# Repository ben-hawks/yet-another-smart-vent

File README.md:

# Yet Another Smart Vent

This project contains most everything needed to 3D print, assemble, and flash an ESPHome/MQTT Smart Vent.

[Here is a short video demonstration on YouTube.](https://youtu.be/ANneINQjgso) 
(Consider subscribing for future updates)

## Getting Started
1. Electronics:
    - [Components List](/docs/ELECTRONIC_COMPONENTS.md)
    - [Assembly Instructions](/docs/ELECTRONICS_ASSEMBLY.md)
2. 3D Printing:
    - [Printing Advice](/docs/VENT_PRINTING.md)
    - [STLs](https://www.printables.com/social/337332-tonyb/collections/241144?o=download_count):
        - [2x6 Vent](https://www.printables.com/model/347800-yet-another-smart-vent-2x6)
        - [2x10 Vent](https://www.printables.com/model/259777-yet-another-smart-vent-2x10)
        - [2x12 Vent](https://www.printables.com/model/260300-yet-another-smart-vent-2x12)
        - [3x10 Vent](https://www.printables.com/model/262311-yet-another-smart-vent-3x10)
        - [4x10 Vent](https://www.printables.com/model/259241-yet-another-smart-vent-4x10)
        - [4x12 Vent](https://www.printables.com/model/259924-yet-another-smart-vent-4x12)
        - [4x14 Vent](https://www.printables.com/model/334635-yet-another-smart-vent-4x14)
        - [6x8   Vent](https://www.printables.com/model/264778-yet-another-smart-vent-6x8)
        - [6x10 Vent](https://www.printables.com/model/259323-yet-another-smart-vent-6x10)
        - [6x12 Vent](https://www.printables.com/model/259622-yet-another-smart-vent-6x12)
        - [ESP D1 Mini Shield Solder Spacer](https://www.printables.com/model/259295-esp-d1-mini-shield-solder-spacer)
    - [Assembly Instructions](/docs/VENT_ASSEMBLY.md)
3. [Compile and Upload Instructions](/docs/COMPILE_AND_UPLOAD.md)
4. [Setup and Testing](/docs/SETUP_AND_TESTING.md)
6. [Implementation Options](/docs/IMPLEMENTATION_OPTIONS.md)

## Battery + Thread variant (work in progress)
A battery-powered 2x12 variant using a Seeed XIAO ESP32-C6 on Thread, with a
power-gated servo and an original parametric OpenSCAD model built around M3
heat-set inserts. See [docs/BATTERY_THREAD.md](/docs/BATTERY_THREAD.md).
A matching Thread rewrite of Delta Tango (supply/return temperature + a vent
safety blueprint) lives in [delta-tango/](/delta-tango/README.md).

A 6" round **ceiling** vent with louvers and a battery pod beside it:
[docs/ROUND_CEILING_VENT.md](/docs/ROUND_CEILING_VENT.md).

## Important Recommendations
- It is recommended that you pair this vent with a system that can [measure and monitor Delta T](https://www.youtube.com/watch?v=_pD-rRCNv8k) (the difference in HVAC return air temperature and supply air temperature). Check out the [Delta Tango](https://github.com/BrobstonCreations/delta-tango) project.
- It is recommended to install a [Static Pressure Regulating Damper](https://www.zonefirst.com/product/sprddd/), which goes between the return air plenum and the supply air plenum. This damper acts as a bypass and will open or close relative to the backpressure change created by opening and closing vents. This will relieve the majority of the back pressure that is created by closing vents and will help to ensure the longevity of the blower.

## Future Features
- Create 8x14 variation.
- Fix a small bug where ESPHome's Servo Position does not match up with the Servo's Potentiometer's position after physically moving the vent's louvers.
- Investigate power saving options for battery pack use.
- Add functionality to open vent if the central vent control system goes offline.
- Experiment with 12x12 vent.

## Philosophy
- Local Control
- External Integration
- Easy of Use
- Community Feedback
- Community Contributions
- Agile, Lean, and Extreme Programming Practices
- Mostly Decentralized Manufacturing

## Pull Requests
Pull Requests are always welcome. I would recommend starting with an [issue](https://github.com/TonyBrobston/yet-another-smart-vent/issues), so that we can discuss viability and implementation.

## Issues
Feel free to open an [issue](https://github.com/TonyBrobston/yet-another-smart-vent/issues) and I will respond as I have time. The hope is to create a system that gives consumers what they want, your feedback is important. 

## Build
If you want to build this manually using docker, run this the command from within this git repo cloned to your machine: 
```
docker run -v .:/config esphome/esphome compile yet-another-smart-vent-dfrobot-dms-mg90-a.yaml
```
After this command runs, `firmware.bin` will be created at this path from the current directory: `.esphome/build/yet-another-smart-vent/.pioenvs/yet-another-smart-vent/firmware.bin`.

## Support
If you like the work I do and want to give back, consider [buying me a coffee ☕](https://www.buymeacoffee.com/brocreates) or making a donation via [PayPal](https://www.paypal.com/donate/?hosted_button_id=BXK8JW6A2FZLE) or [Stripe](https://buy.stripe.com/7sI7t03JC9GUf4c6oo).

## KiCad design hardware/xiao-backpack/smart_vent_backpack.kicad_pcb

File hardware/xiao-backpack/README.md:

# Smart Vent XIAO backpack (KiCad)

A 48 × 19 mm two-layer board that holds all of the vent's auxiliary
circuitry. The XIAO ESP32-C6 plugs onto it with its two 1×7 headers.

**Status: v0.2, routed and checked, not yet built.** It was autorouted with
Freerouting from `fab/smart_vent_backpack.dsn`; the result is in
`fab/smart_vent_backpack.ses`. After importing:
- every net is connected (0 unconnected pads)
- KiCad DRC reports 0 violations (KiCad 7 here, and KiCad 10 on a second
  machine), against fab rules of 0.3 mm to the edge, 0.15 mm clearance and
  0.13 mm minimum track
- the PCB's netlist matches the schematic's
- an independent review with KiCad 10 found no blockers (see
  [Design review notes](#design-review-notes-v02))

Power nets (VBAT_RAW, VBAT, GND, VSW, SW, V5) are 0.6 mm, narrowing to
0.45 mm only for a few millimetres at pads. Ground is poured on both
layers. Order with [`fab/gerbers.zip`](fab/gerbers.zip) (2 layers, 1.6 mm,
1 oz, any colour; JLCPCB's standard tier is enough).

## Circuit

| Block | Parts | Notes |
|---|---|---|
| Battery in | J1 (JST-PH 2 mm), Q1 AO3401A, TP1/TP2 | Q1 blocks a cell fitted backwards and conducts both ways otherwise. TP1/TP2 are wire pads. Run short wires through the window to the XIAO's BAT+/BAT− pads, which charge the cell over USB-C |
| Servo power switch | U1 TPS22917 load switch, C1, C2 (1 nF, CT to VIN: about 1.6 ms soft start), R1 (keeps it off) | Cuts the cell off completely between moves (nanoamp leakage). Its ON pin is XIAO **D3** |
| 5 V boost | U2 MT3608, L1 10 µH, D1 SS34, C3–C5 22 µF, R2/R3 | Vout = 0.6 V × (1 + 51k/6.8k) = 5.1 V (both JLCPCB basic parts). Only powered while U1 is on |
| Servo | J2: GND, +5V, SIG, FB | SIG from **D2** through R8 (330 Ω). FB through a 10k/20k divider (R6/R7, C7 filter) to **D1**: 5.1 V → 3.4 V. Feetech's sheet shows the FT90M-FB's feedback reaching **4.45 V**, so it must be divided |
| Battery sense | R4/R5 1M/1M, C6 | To **D0**. Draws about 2 µA |
| Limit switch | J3 | Fed from **D3** through R9 (1 kΩ), returns to **D4** with R10 (100 kΩ) pull-down. Only live while the servo is powered |

These pins match `common/smart-vent-thread-battery-base.yaml`, so the
firmware needs no changes.

## Building it

- All passives are 0805 (1206 for the 22 µF capacitors) with hand-solder
  pads. Both ICs are SOT-23-6. Parts list: [`fab/bom.csv`](fab/bom.csv).
- **Inductor:** any shielded 10 µH in 6 × 6 mm with a saturation current of
  2.5 A or more. A stalled servo pulls about 1.3 A from the cell through the
  boost converter.
- **Battery connector polarity:** JST-PH leads aren't standardized. Pin 1
  (square pad) is **+**. Check your cell's leads before plugging in.
- Mount the XIAO on the **top** with standard headers. Only the 0805 parts
  sit underneath it. Solder the battery wires to the XIAO's BAT pads before
  stacking the boards.

## JLCPCB assembly (PCBA)

Upload these three to JLCPCB with **PCB Assembly** turned on (top side, Economic):

| File | What |
|---|---|
| [`fab/gerbers.zip`](fab/gerbers.zip) | Board |
| [`fab/jlcpcb/bom_jlcpcb.csv`](fab/jlcpcb/bom_jlcpcb.csv) | Comment, Designator, Footprint, LCSC Part # |
| [`fab/jlcpcb/cpl_jlcpcb.csv`](fab/jlcpcb/cpl_jlcpcb.csv) | Designator, Mid X, Mid Y, Layer, Rotation |

- **What JLCPCB places:** all 22 SMD parts. 14 BOM lines are JLCPCB
  **Basic** parts. 3 are **Extended**, which carries a feeder fee per order:
  TPS22917DBVR (C2681320), MT3608 (C84817) and SRN6045TA-100M (C2046332).
  Part numbers and stock were checked against JLCPCB's parts library on
  2026-11-01.
- **Left for you:** the through-hole parts (J1 JST-PH C131337, J2, J3, the
  XIAO socket headers and the TP1/TP2 wire pads) aren't in the files. Solder
  them yourself, or add them to the order if you want JLCPCB's through-hole
  service.
- **Rotations:** the CPL applies JLCPCB's usual +180° for SOT-23 parts. In
  JLCPCB's placement preview, **check that pin 1 of U1 and U2 and the
  cathode band of D1 sit on the marked pads** before confirming. Rotate any
  part that's off there; the files don't need regenerating.

## Design review notes (v0.2)

- **C2 now goes from CT to VIN and is fitted** (TI SLVSDW8B, Table 6-1).
  v0.1 wired it to GND and left it off. With CT open the switch rises in
  about 65 µs, which charges C3–C5 through L1 and D1 at roughly 2 A, close
  to the TPS22917's 2.5 A pulse rating. With 1 nF it rises in about 1.6 ms
  and the inrush is about 0.15 A.
- **Q1 (AO3401A) is new:** drain to the cell, source to the board, gate to
  GND. A reversed cell leaves it off. Don't plug in USB while a cell is
  reversed: the XIAO's charger would turn Q1 on.
- The servo header's pin labels (G, 5V, S, FB) are on the **back**
  silkscreen; Q1 and C2 took their place on the front.
- **Independent KiCad 10 review (2026-11-13):** pinouts of U1, U2, Q1 and
  D1, the XIAO pin map, all three dividers and the five LCSC numbers for
  the active parts and inductor were re-checked against datasheets and
  distributor listings; no errors. KiCad's ERC flags U1's QOD pin tied to
  VOUT and an analyzer flags U2's EN tied to IN; both are the
  manufacturers' documented connections. Its three layout points were
  checked here: one 0.125 mm neck on LIMIT is now 0.13 mm (JLCPCB's
  standard minimum is 0.127 mm); the "0.1 mm from the edge" on J2/J3 is
  their courtyard, and the nearest pad copper to any edge is 0.68 mm; the
  0.45 mm necks on the battery nets total under 8 mm.
- The router is now given a 0.35 mm keep-out around the battery window and
  along the board edges, so it can't hug them (it did in v0.1).
- **Checked against datasheets:** the TPS22917 and MT3608 pinouts, the
  MT3608 FB voltage (0.6 V), EN tied to the input (allowed), and the input
  range (2–24 V). GPIO0/1 are ADC1 channels 0/1. None of the pins used
  (GPIO0, 1, 2, 21, 22) is a strapping pin; those are GPIO4, 5, 8, 9 and 15.
- **Fit in the vent tower:** solder the XIAO **directly** onto its male
  headers (no female sockets), and use **right-angle** headers for J2/J3.
  The pads are the same, and this keeps the stack inside the 17 mm between
  the cell holder and the partition (1 mm and 0.9 mm clearance). Trim the
  through-hole leads on the back to about 2 mm.
- **Battery wire window:** its position comes from Seeed's description
  ("near D5 / D8"). If the BAT pads end up off the window, route the two
  wires around the board edge to TP1/TP2.

## Hand soldering

Everything is hand-solderable with a fine-tip iron, flux and tweezers:
- 0805 and 1206 parts on KiCad's hand-solder pads.
- Both ICs are SOT-23-6 (0.95 mm pitch) on the hand-solder variant.
- The inductor's terminals are mostly under its body, so its pads extend
  0.8 mm past the Bourns land pattern for the iron. Tin one pad, place the
  part, then heat the extended pad until solder wicks under.
- No vias sit in pads, and ground pads use thermal spokes, so they heat up
  normally.

Suggested order:
1. The low parts under the XIAO (R1, R4–R10, C6, C7). They're unreachable
   once the XIAO is fitted.
2. Q1, U1, U2, C1–C5, R2, R3, D1, then L1.
3. Before fitting the XIAO, check that 5 V comes up: connect the cell and
   pull D3 (SRV_EN) high through about 1 kΩ. J2 pin 2 should read about
   5.1 V, and about 0 V again once D3 is released.
4. J1, J2 and J3 (right-angle), then the XIAO, soldered directly on its
   male headers. Solder the battery wires to
   the XIAO's BAT pads, pass them through the window, and solder them to
   TP1 (+) and TP2 (−).

## Routing

`generate.py` builds everything from one parts table: the schematic (net
labels on every pin), the placed PCB, net classes (0.6 mm for power nets),
ground pours, Gerbers, the parts list, and the checks (schematic vs PCB
nets, DRC).

```bash
/usr/bin/python3 generate.py                              # place, write fab/smart_vent_backpack.dsn
# route fab/smart_vent_backpack.dsn with Freerouting (or similar) -> .ses
/usr/bin/python3 generate.py --ses fab/smart_vent_backpack.ses   # import routes, pour, DRC, Gerbers
# GND tracks that hug the battery window are dropped on import (the pours carry GND)
```

The router's output can also be imported straight into KiCad (**File →
Import → Specctra Session**) on the generated `.kicad_pcb`.

Requires KiCad 7 or 8. On KiCad 10 the script stops: the Bourns inductor
footprint it adapts has changed and the `Q_PMOS_GSD` symbol was renamed.
The generated project files open fine in KiCad 10. Set `KICAD7_FOOTPRINT_DIR` if KiCad's global
libraries aren't configured.

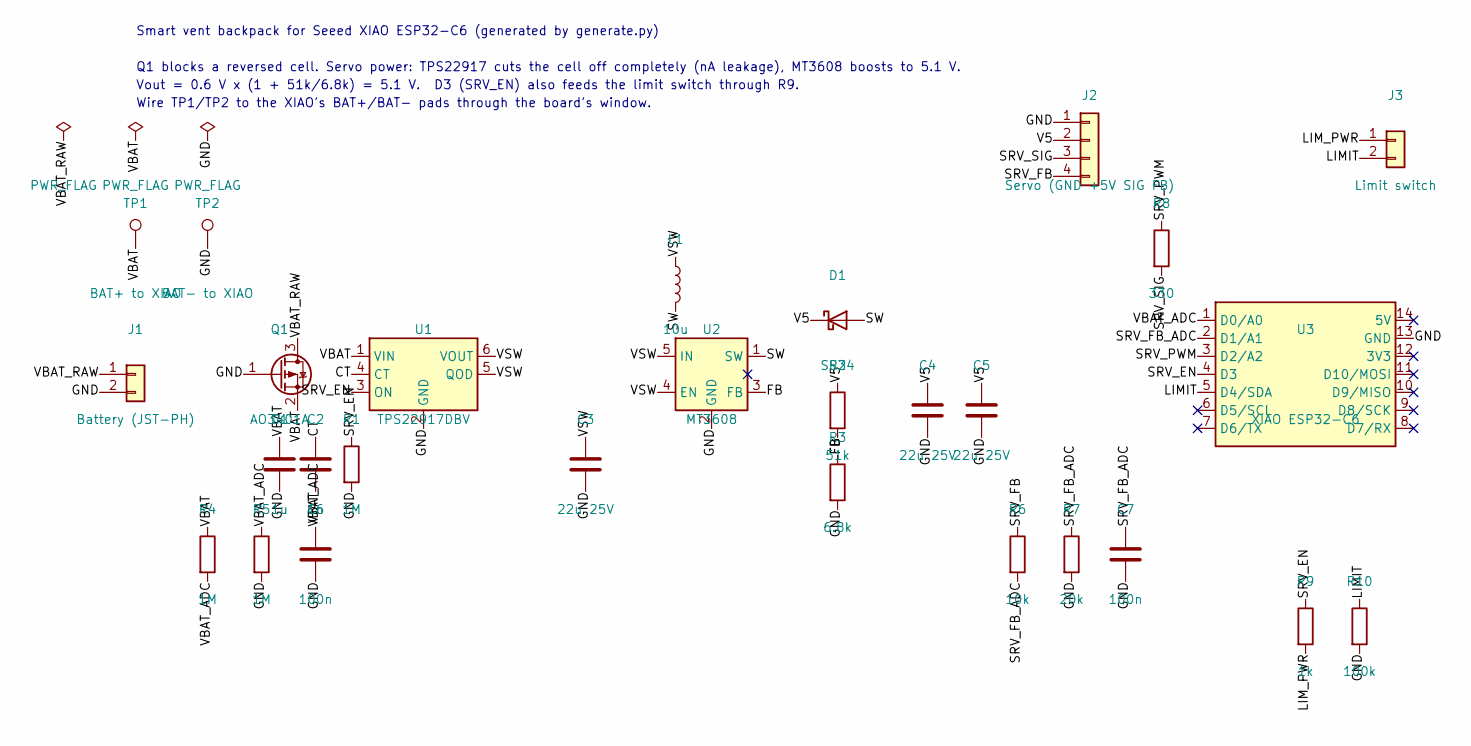
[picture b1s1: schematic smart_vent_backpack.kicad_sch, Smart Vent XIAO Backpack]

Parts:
C1: 1u; C_0805_2012Metric_Pad1.18x1.45mm_HandSolder
C2: 1n; C_0805_2012Metric_Pad1.18x1.45mm_HandSolder
C3, C4, C5: 22u 25V; C_1206_3216Metric_Pad1.33x1.80mm_HandSolder
C6, C7: 100n; C_0805_2012Metric_Pad1.18x1.45mm_HandSolder
D1: SS34; D_SMA_Handsoldering
J1: Battery (JST-PH); JST_PH_B2B-PH-K_1x02_P2.00mm_Vertical
J2: Servo (GND +5V SIG FB); PinHeader_1x04_P2.54mm_Vertical
J3: Limit switch; PinHeader_1x02_P2.54mm_Vertical
L1: 10u; L_Bourns_SRN6045TA_HandSolder
Q1: AO3401A; SOT-23
R1, R4, R5: 1M; R_0805_2012Metric_Pad1.20x1.40mm_HandSolder
R2: 51k; R_0805_2012Metric_Pad1.20x1.40mm_HandSolder
R3: 6.8k; R_0805_2012Metric_Pad1.20x1.40mm_HandSolder
R6: 10k; R_0805_2012Metric_Pad1.20x1.40mm_HandSolder
R7: 20k; R_0805_2012Metric_Pad1.20x1.40mm_HandSolder
R8: 330; R_0805_2012Metric_Pad1.20x1.40mm_HandSolder
R9: 1k; R_0805_2012Metric_Pad1.20x1.40mm_HandSolder
R10: 100k; R_0805_2012Metric_Pad1.20x1.40mm_HandSolder
TP1: BAT+ to XIAO; TestPoint_THTPad_1.5x1.5mm_Drill0.7mm
TP2: BAT- to XIAO; TestPoint_THTPad_1.5x1.5mm_Drill0.7mm
U1: TPS22917DBV; SOT-23-6_Handsoldering
U2: MT3608; SOT-23-6_Handsoldering
U3: XIAO ESP32-C6; XIAO_ESP32C6_Backpack

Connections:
CT: C2.1, U1.4 (CT)
FB: R2.2, R3.1, U2.3 (FB)
GND: C1.2, C3.2, C4.2, C5.2, C6.2, C7.2, J1.2, J2.1, Q1.1 (G), R1.2, R3.2, R5.2, R7.2, R10.2, TP2.1, U1.2 (GND), U2.2 (GND), U3.13 (GND)
LIMIT: J3.2, R10.1, U3.5 (D4/SDA)
LIM_PWR: J3.1, R9.2
SRV_EN: R1.1, R9.1, U1.3 (ON), U3.4 (D3)
SRV_FB: J2.4, R6.1
SRV_FB_ADC: C7.1, R6.2, R7.1, U3.2 (D1/A1)
SRV_PWM: R8.1, U3.3 (D2/A2)
SRV_SIG: J2.3, R8.2
SW: D1.2 (A), L1.2, U2.1 (SW)
V5: C4.1, C5.1, D1.1 (K), J2.2, R2.1
VBAT: C1.1, C2.2, Q1.2 (S), R4.1, TP1.1, U1.1 (VIN)
VBAT_ADC: C6.1, R4.2, R5.1, U3.1 (D0/A0)
VBAT_RAW: J1.1, Q1.3 (D)
VSW: C3.1, L1.1, U1.5 (QOD), U1.6 (VOUT), U2.4 (EN), U2.5 (IN)

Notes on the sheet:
Smart vent backpack for Seeed XIAO ESP32-C6 (generated by generate.py)
Q1 blocks a reversed cell. Servo power: TPS22917 cuts the cell off completely (nA leakage), MT3608 boosts to 5.1 V.
Vout = 0.6 V x (1 + 51k/6.8k) = 5.1 V. D3 (SRV_EN) also feeds the limit switch through R9.
Wire TP1/TP2 to the XIAO's BAT+/BAT- pads through the board's window.

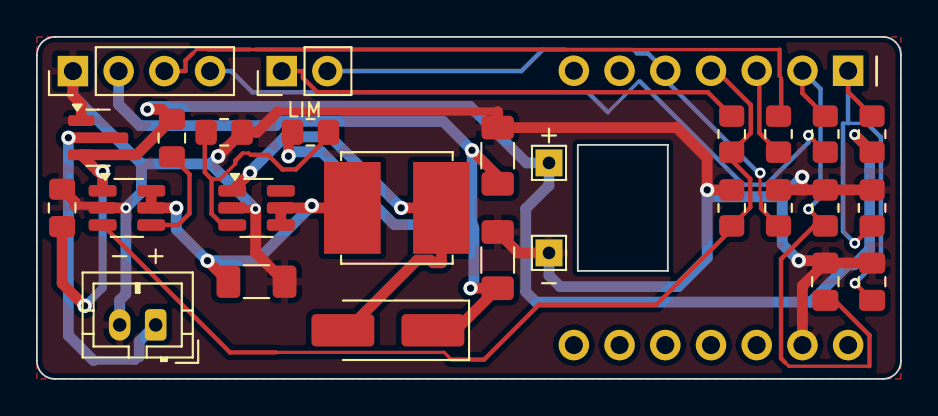
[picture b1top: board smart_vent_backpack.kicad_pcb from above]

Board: 2 copper layers, 48.0 x 19.0 mm, 28 parts (0 on the bottom side), 16 nets.

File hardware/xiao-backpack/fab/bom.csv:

References,Qty,Value,Footprint,Notes
C1,1,1u,C_0805_2012Metric_Pad1.18x1.45mm_HandSolder,0805
C2,1,1n,C_0805_2012Metric_Pad1.18x1.45mm_HandSolder,0805
C3 C4 C5,3,22u 25V,C_1206_3216Metric_Pad1.33x1.80mm_HandSolder,22 uF 25 V X5R 1206
C7 C6,2,100n,C_0805_2012Metric_Pad1.18x1.45mm_HandSolder,0805
D1,1,SS34,D_SMA_Handsoldering,"SS34 (40 V 3 A Schottky, SMA) or SS24"
J1,1,Battery (JST-PH),JST_PH_B2B-PH-K_1x02_P2.00mm_Vertical,JST B2B-PH-K-S (2 mm). CHECK the battery lead polarity: pin 1 = +
J2,1,Servo (GND +5V SIG FB),PinHeader_1x04_P2.54mm_Vertical,1x4 2.54 mm header
J3,1,Limit switch,PinHeader_1x02_P2.54mm_Vertical,1x2 2.54 mm header
L1,1,10u,L_Bourns_SRN6045TA_HandSolder,"Bourns SRN6045TA-100M (10 uH, Isat 4.6 A, 52 mOhm); footprint is its land pattern with pads extended for hand soldering"
Q1,1,AO3401A,SOT-23,AO3401A P-MOSFET (SOT-23): reverse-polarity protection
R1 R4 R5,3,1M,R_0805_2012Metric_Pad1.20x1.40mm_HandSolder,0805
R10,1,100k,R_0805_2012Metric_Pad1.20x1.40mm_HandSolder,0805
R2,1,51k,R_0805_2012Metric_Pad1.20x1.40mm_HandSolder,0805
R3,1,6.8k,R_0805_2012Metric_Pad1.20x1.40mm_HandSolder,0805
R6,1,10k,R_0805_2012Metric_Pad1.20x1.40mm_HandSolder,0805
R7,1,20k,R_0805_2012Metric_Pad1.20x1.40mm_HandSolder,0805
R8,1,330,R_0805_2012Metric_Pad1.20x1.40mm_HandSolder,0805
R9,1,1k,R_0805_2012Metric_Pad1.20x1.40mm_HandSolder,0805
TP1,1,BAT+ to XIAO,TestPoint_THTPad_1.5x1.5mm_Drill0.7mm,wire pad
TP2,1,BAT- to XIAO,TestPoint_THTPad_1.5x1.5mm_Drill0.7mm,wire pad
U1,1,TPS22917DBV,SOT-23-6_Handsoldering,TI TPS22917DBVR load switch
U2,1,MT3608,SOT-23-6_Handsoldering,MT3608 boost (SOT-23-6)
